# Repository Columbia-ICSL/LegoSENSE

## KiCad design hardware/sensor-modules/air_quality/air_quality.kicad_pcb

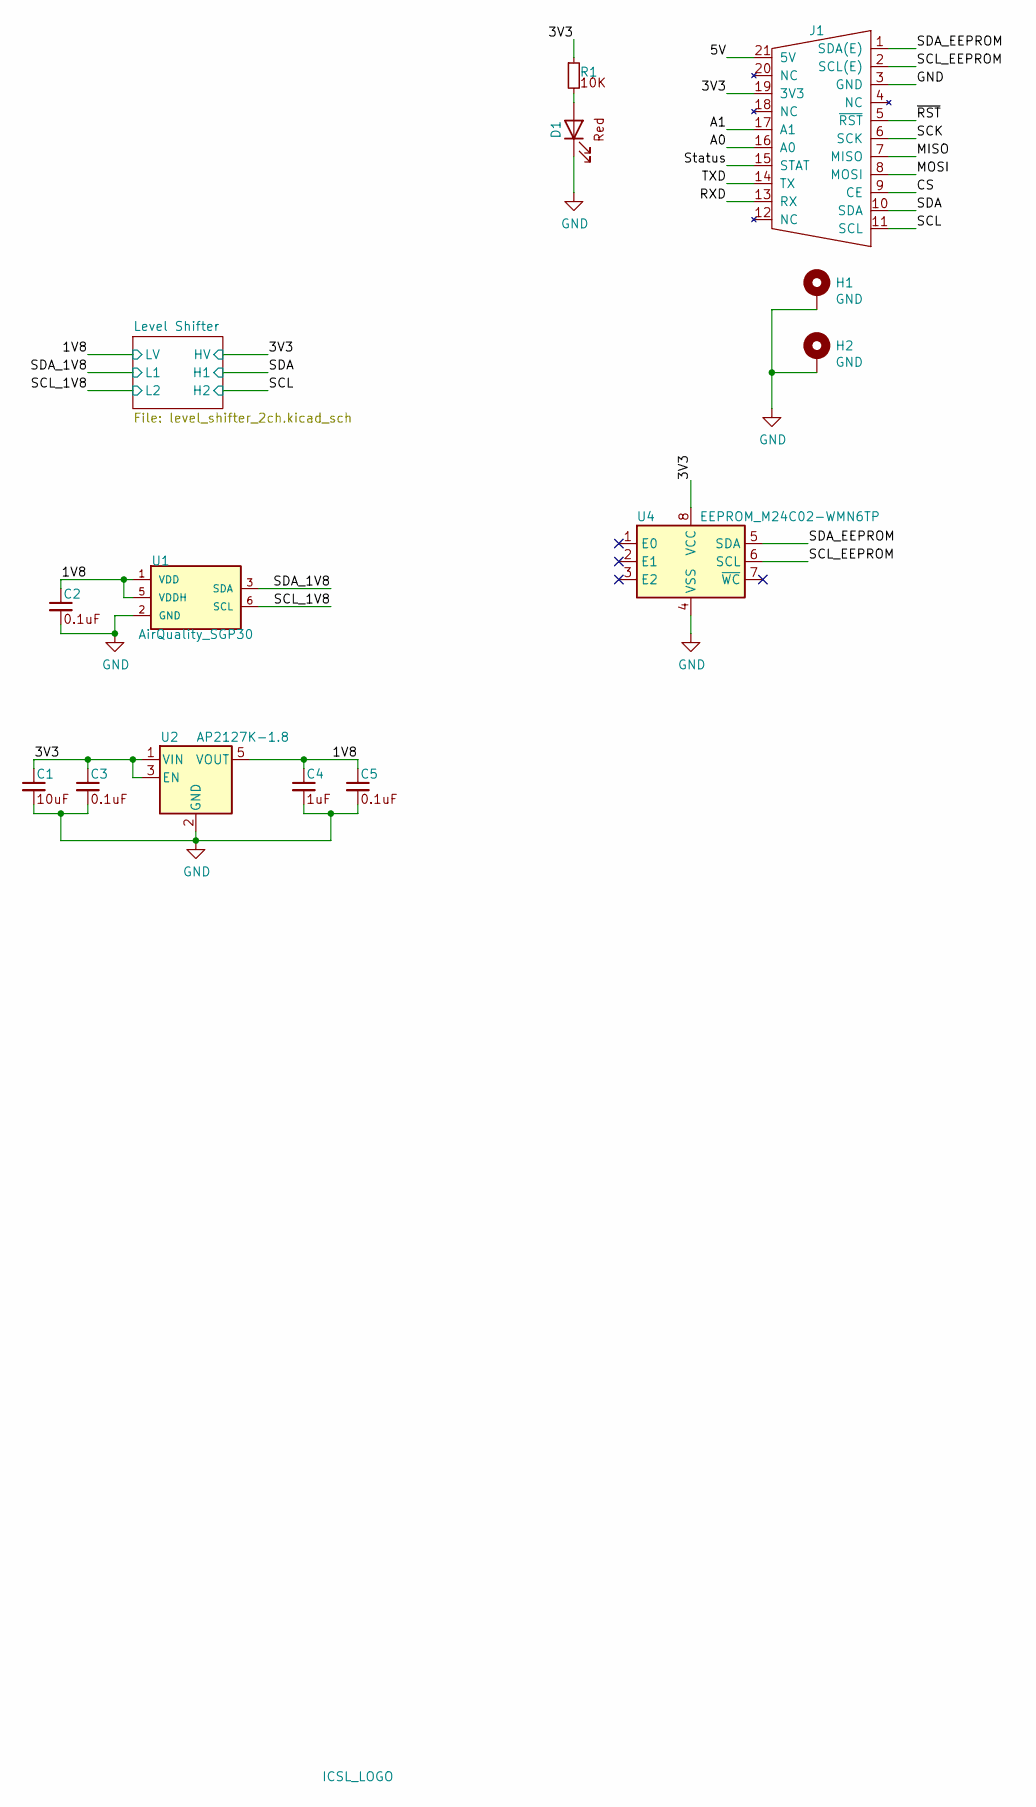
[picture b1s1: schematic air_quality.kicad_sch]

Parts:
C1: C_0603_10uF_10V; C_0603_1608Metric; MFR Part# CL10A106KP8NNNC; LCSC C19702
C2, C3, C5: C_0402_0.1uF_16V; C_0402_1005Metric; MFR Part# CL05B104KO5NNNC; LCSC C1525
C4: C_0402_1uF_25V; C_0402_1005Metric; MFR Part# CL05A105KA5NQNC; LCSC C52923
D1: LED_0603_Red; LED_0603_1608Metric; MFR Part# KT-0603R; LCSC C2286
H1, H2: GND; M1502-B-2545-AL-TOP
J1: Amphenol_91911-31321_plug; Amphenol_91911-31321LF_PLUG; LCSC C9900009023
R1: R_0402_10K; R_0402_1005Metric; MFR Part# 0402WGF1002TCE; LCSC C25744
U1: AirQuality_SGP30; SGP30; MFR Part# SGP30-2.5k; LCSC C514454
U2: AP2127K-1.8; SOT-23-5; MCF Part# AP2127K-1.8TRG1; LCSC C151375
U3: ICSL_LOGO; icsl_logo
U4: EEPROM_M24C02-WMN6TP; SOIC-8_3.9x4.9mm_P1.27mm; MFR Part# M24C02-WMN6TP; LCSC C7562

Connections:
/1V8: C2.1, C4.1, C5.1, U1.1 (VDD), U1.5 (VDDH), U2.5 (VOUT); also elsewhere on the board
/3V3: C1.1, C3.1, J1.19 (3V3), R1.1, U2.1 (VIN), U2.3 (EN), U4.8 (VCC); also elsewhere on the board
/5V: J1.21 (5V)
/A0: J1.16 (A0)
/A1: J1.17 (A1)
/CS: J1.9 (CE)
/MISO: J1.7 (MISO)
/MOSI: J1.8 (MOSI)
/RXD: J1.13 (RX)
/SCK: J1.6 (SCK)
/SCL: J1.11 (SCL); also elsewhere on the board
/SCL_1V8: U1.6 (SCL); also elsewhere on the board
/SCL_EEPROM: J1.2 (SCL(E)), U4.6 (SCL)
/SDA: J1.10 (SDA); also elsewhere on the board
/SDA_1V8: U1.3 (SDA); also elsewhere on the board
/SDA_EEPROM: J1.1 (SDA(E)), U4.5 (SDA)
/Status: J1.15 (STAT)
/TXD: J1.14 (TX)
/~RST: J1.5 (~RST)
GND: C1.2, C2.2, C3.2, C4.2, C5.2, D1.1 (K), H1.1, H2.1, J1.3 (GND), U1.2 (GND), U1.4 (R), U1.7 (EPAD), U2.2 (GND), U4.4 (VSS)
unnamed: D1.2 (A), R1.2

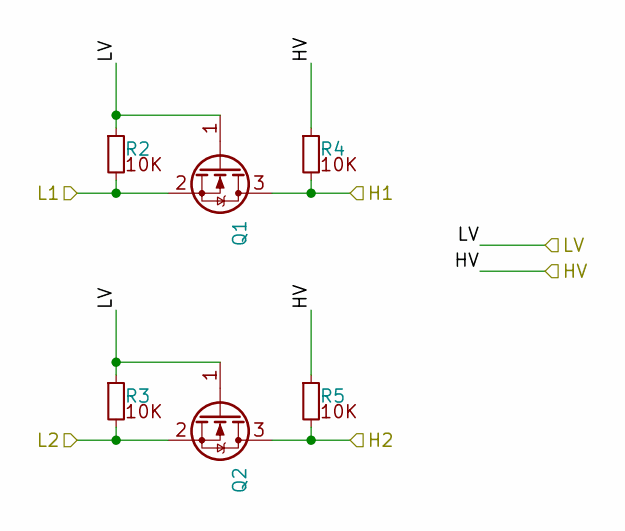
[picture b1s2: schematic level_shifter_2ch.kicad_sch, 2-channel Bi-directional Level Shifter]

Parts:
Q1, Q2: NMOS_BSS138; SOT-23; MFR Part# BSS138; LCSC C78284
R2, R3, R4, R5: R_0402_10K; R_0402_1005Metric; MFR Part# 0402WGF1002TCE; LCSC C25744

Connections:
/1V8: Q1.1 (G), Q2.1 (G), R2.1, R3.1; also elsewhere on the board
/3V3: R4.1, R5.1; also elsewhere on the board
/SCL: Q2.3 (D), R5.2; also elsewhere on the board
/SCL_1V8: Q2.2 (S), R3.2; also elsewhere on the board
/SDA: Q1.3 (D), R4.2; also elsewhere on the board
/SDA_1V8: Q1.2 (S), R2.2; also elsewhere on the board

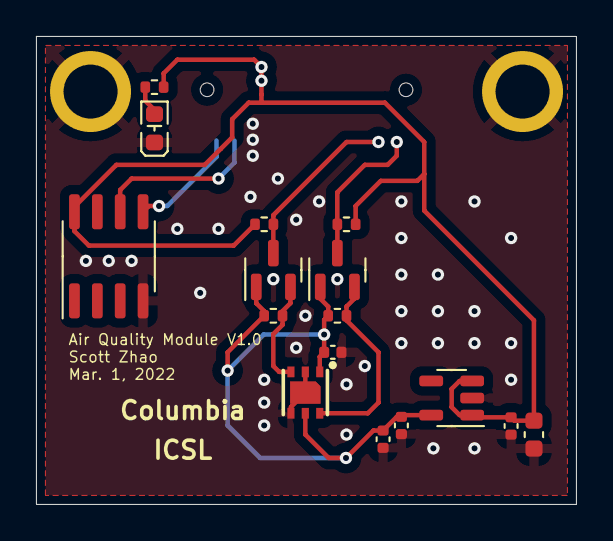
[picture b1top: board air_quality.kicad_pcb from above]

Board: 4 copper layers, 30.0 x 26.0 mm, 20 parts (1 on the bottom side), 10 nets.

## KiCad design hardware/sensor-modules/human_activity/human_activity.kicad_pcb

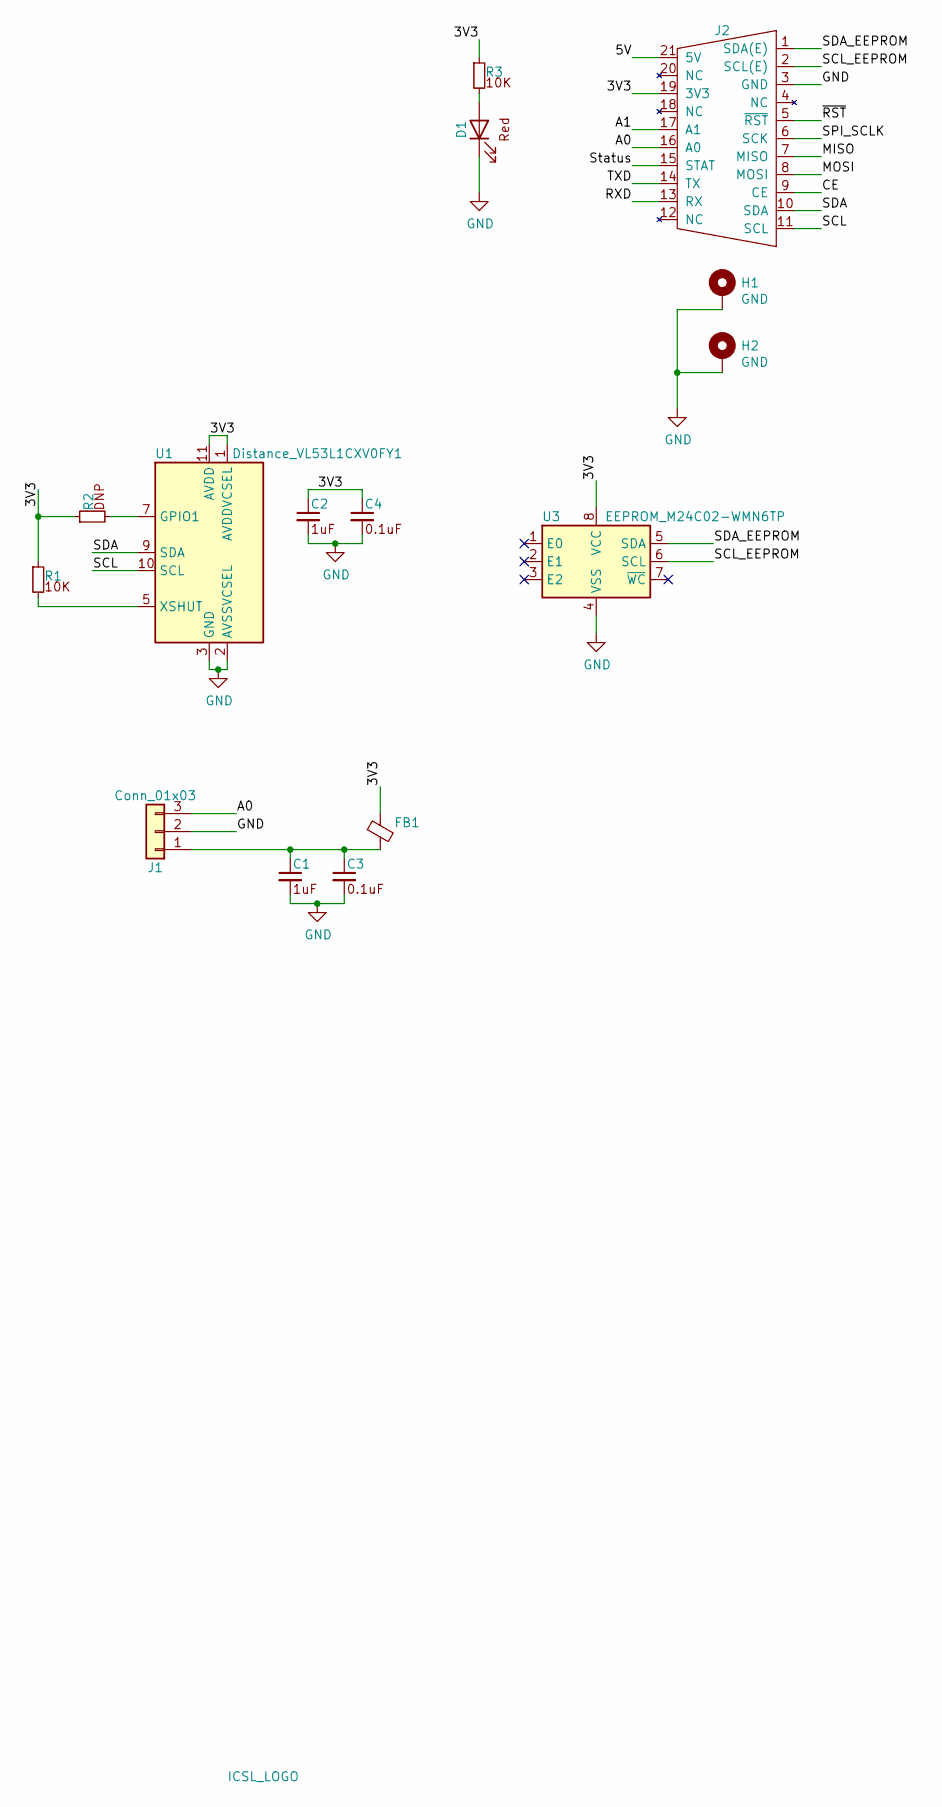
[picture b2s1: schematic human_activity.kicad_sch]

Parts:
C1, C2: C_0402_1uF_25V; C_0402_1005Metric; MFR Part# CL05A105KA5NQNC; LCSC C52923
C3, C4: C_0402_0.1uF_16V; C_0402_1005Metric; MFR Part# CL05B104KO5NNNC; LCSC C1525
D1: LED_0603_Red; LED_0603_1608Metric; MFR Part# KT-0603R; LCSC C2286
FB1: B_0805_600R; L_0805_2012Metric; MFR Part# GZ2012D601TF; LCSC C1017
H1, H2: GND; M1502-B-2545-AL-TOP
J1: Conn_01x03; PinHeader_1x03_P2.54mm_Vertical
J2: Amphenol_91911-31321_plug; Amphenol_91911-31321LF_PLUG; LCSC C9900009023
R1, R3: R_0402_10K; R_0402_1005Metric; MFR Part# 0402WGF1002TCE; LCSC C25744
R2: R_0402_DNP; R_0402_1005Metric
U1: Distance_VL53L1CXV0FY1; ST_VL53L1X; MFR Part# VL53L1CXV0FY/1; LCSC C190004
U2: ICSL_LOGO; icsl_logo
U3: EEPROM_M24C02-WMN6TP; SOIC-8_3.9x4.9mm_P1.27mm; MFR Part# M24C02-WMN6TP; LCSC C7562

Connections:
/3V3: C2.1, C4.1, FB1.1, J2.19 (3V3), R1.1, R2.1, R3.1, U1.1 (AVDDVCSEL), U1.11 (AVDD), U3.8 (VCC)
/5V: J2.21 (5V)
/A0: J1.3, J2.16 (A0)
/A1: J2.17 (A1)
/CE: J2.9 (CE)
/MISO: J2.7 (MISO)
/MOSI: J2.8 (MOSI)
/RXD: J2.13 (RX)
/SCL: J2.11 (SCL), U1.10 (SCL)
/SCL_EEPROM: J2.2 (SCL(E)), U3.6 (SCL)
/SDA: J2.10 (SDA), U1.9 (SDA)
/SDA_EEPROM: J2.1 (SDA(E)), U3.5 (SDA)
/SPI_SCLK: J2.6 (SCK)
/Status: J2.15 (STAT)
/TXD: J2.14 (TX)
/~RST: J2.5 (~RST)
GND: C1.2, C2.2, C3.2, C4.2, D1.1 (K), H1.1, H2.1, J1.2, J2.3 (GND), U1.2 (AVSSVCSEL), U1.3 (GND), U1.4 (GND), U1.6 (GND), U1.12 (GND), U3.4 (VSS)
unnamed: C1.1, C3.1, FB1.2, J1.1
unnamed: D1.2 (A), R3.2
unnamed: R1.2, U1.5 (XSHUT)
unnamed: R2.2, U1.7 (GPIO1)

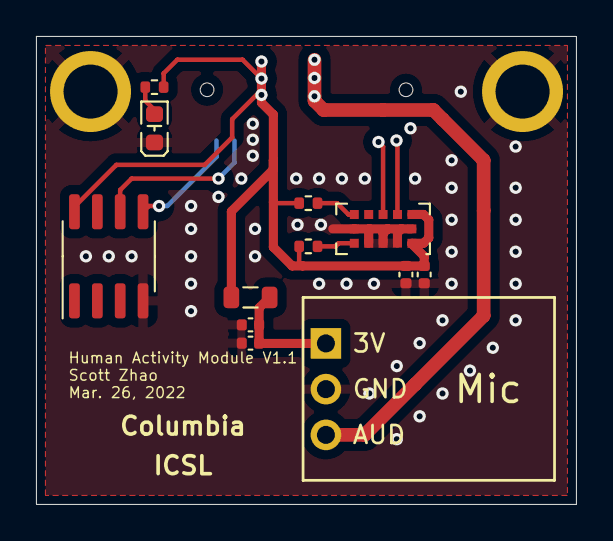
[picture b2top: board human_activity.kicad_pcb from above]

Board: 4 copper layers, 30.0 x 26.0 mm, 16 parts (1 on the bottom side), 11 nets.

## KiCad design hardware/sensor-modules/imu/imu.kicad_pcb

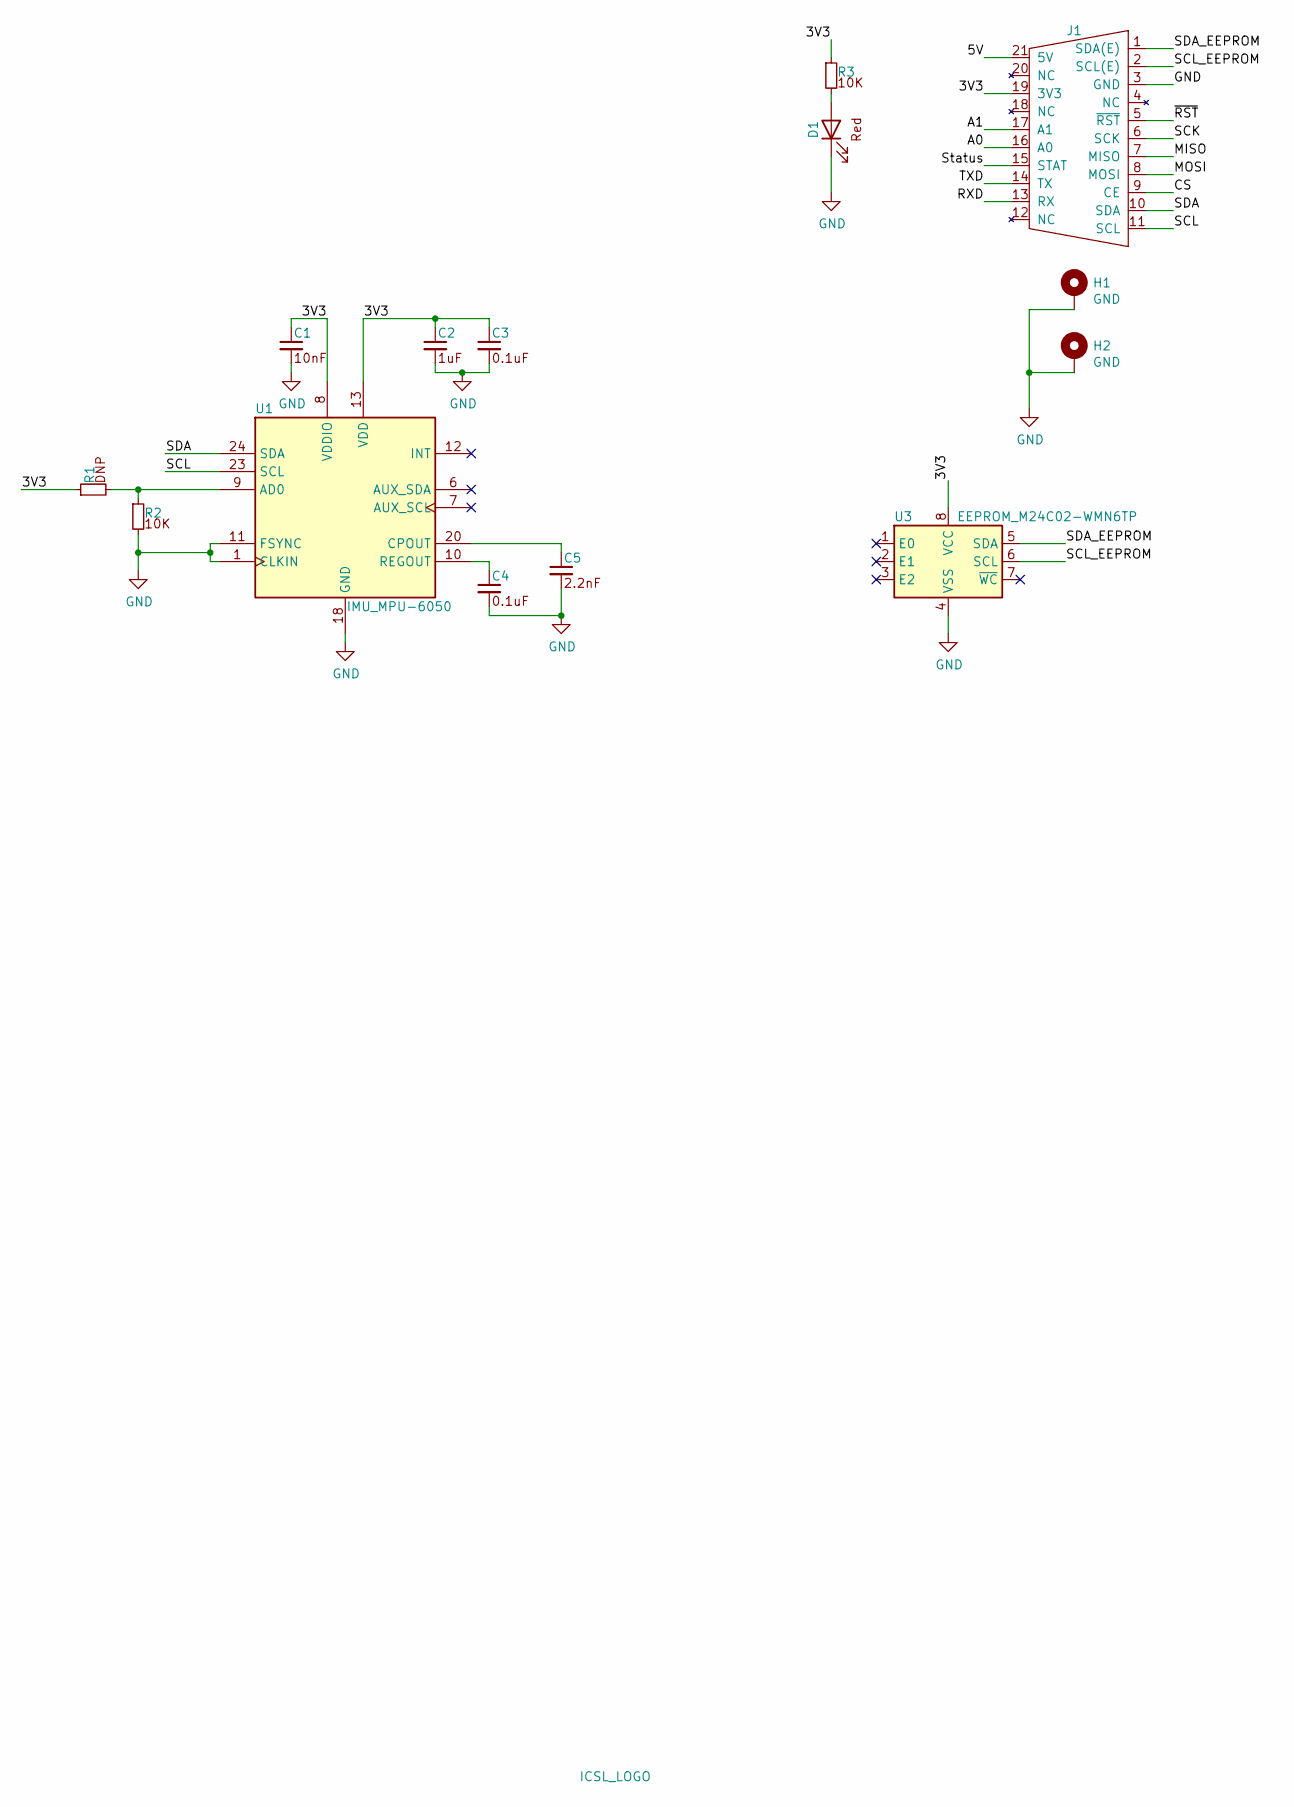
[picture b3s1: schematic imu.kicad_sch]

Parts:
C1: C_0402_10nF_50V; C_0402_1005Metric; MFR Part# CL05B103KB5NNNC; LCSC C15195
C2: C_0402_1uF_25V; C_0402_1005Metric; MFR Part# CL05A105KA5NQNC; LCSC C52923
C3, C4: C_0402_0.1uF_16V; C_0402_1005Metric; MFR Part# CL05B104KO5NNNC; LCSC C1525
C5: C_0402_2.2nF_50V; C_0402_1005Metric; MFR Part# 0402B222K500NT; LCSC C1531
D1: LED_0603_Red; LED_0603_1608Metric; MFR Part# KT-0603R; LCSC C2286
H1, H2: GND; M1502-B-2545-AL-TOP
J1: Amphenol_91911-31321_plug; Amphenol_91911-31321LF_PLUG; LCSC C9900009023
R1: R_0402_DNP; R_0402_1005Metric
R2, R3: R_0402_10K; R_0402_1005Metric; MFR Part# 0402WGF1002TCE; LCSC C25744
U1: IMU_MPU-6050; InvenSense_QFN-24_4x4mm_P0.5mm; MFR Part# MPU-6050; LCSC C24112
U2: ICSL_LOGO; icsl_logo
U3: EEPROM_M24C02-WMN6TP; SOIC-8_3.9x4.9mm_P1.27mm; MFR Part# M24C02-WMN6TP; LCSC C7562

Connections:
/3V3: C1.1, C2.1, C3.1, J1.19 (3V3), R1.1, R3.1, U1.8 (VDDIO), U1.13 (VDD), U3.8 (VCC)
/5V: J1.21 (5V)
/A0: J1.16 (A0)
/A1: J1.17 (A1)
/CS: J1.9 (CE)
/MISO: J1.7 (MISO)
/MOSI: J1.8 (MOSI)
/RXD: J1.13 (RX)
/SCK: J1.6 (SCK)
/SCL: J1.11 (SCL), U1.23 (SCL)
/SCL_EEPROM: J1.2 (SCL(E)), U3.6 (SCL)
/SDA: J1.10 (SDA), U1.24 (SDA)
/SDA_EEPROM: J1.1 (SDA(E)), U3.5 (SDA)
/Status: J1.15 (STAT)
/TXD: J1.14 (TX)
/~RST: J1.5 (~RST)
GND: C1.2, C2.2, C3.2, C4.2, C5.2, D1.1 (K), H1.1, H2.1, J1.3 (GND), R2.2, U1.1 (CLKIN), U1.11 (FSYNC), U1.18 (GND), U1.25 (GND), U3.4 (VSS)
unnamed: C4.1, U1.10 (REGOUT)
unnamed: C5.1, U1.20 (CPOUT)
unnamed: D1.2 (A), R3.2
unnamed: R1.2, R2.1, U1.9 (AD0)

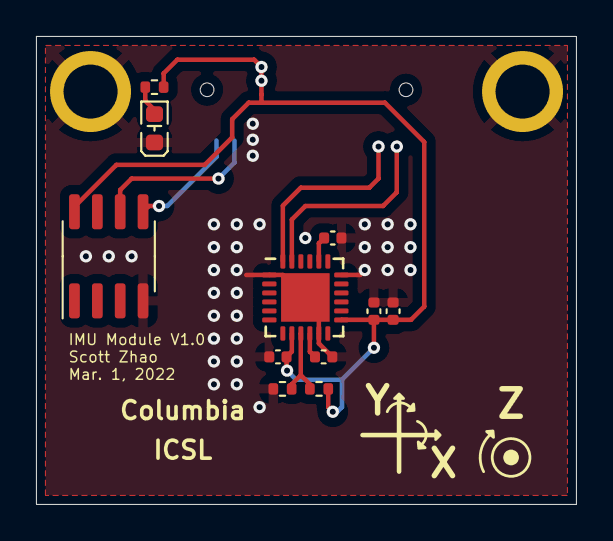
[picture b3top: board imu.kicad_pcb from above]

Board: 4 copper layers, 30.0 x 26.0 mm, 15 parts (1 on the bottom side), 10 nets.
